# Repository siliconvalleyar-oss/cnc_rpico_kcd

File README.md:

# CNC RPico

Controlador CNC basado en Raspberry Pi Pico, diseñado en KiCad.

## Descripción

Proyecto de hardware para control de máquinas CNC utilizando la Raspberry Pi Pico como microcontrolador principal.

## Herramientas

- KiCad 10.0.4
- FreeRouting (autoroute)

## Licencia

GPL v2+

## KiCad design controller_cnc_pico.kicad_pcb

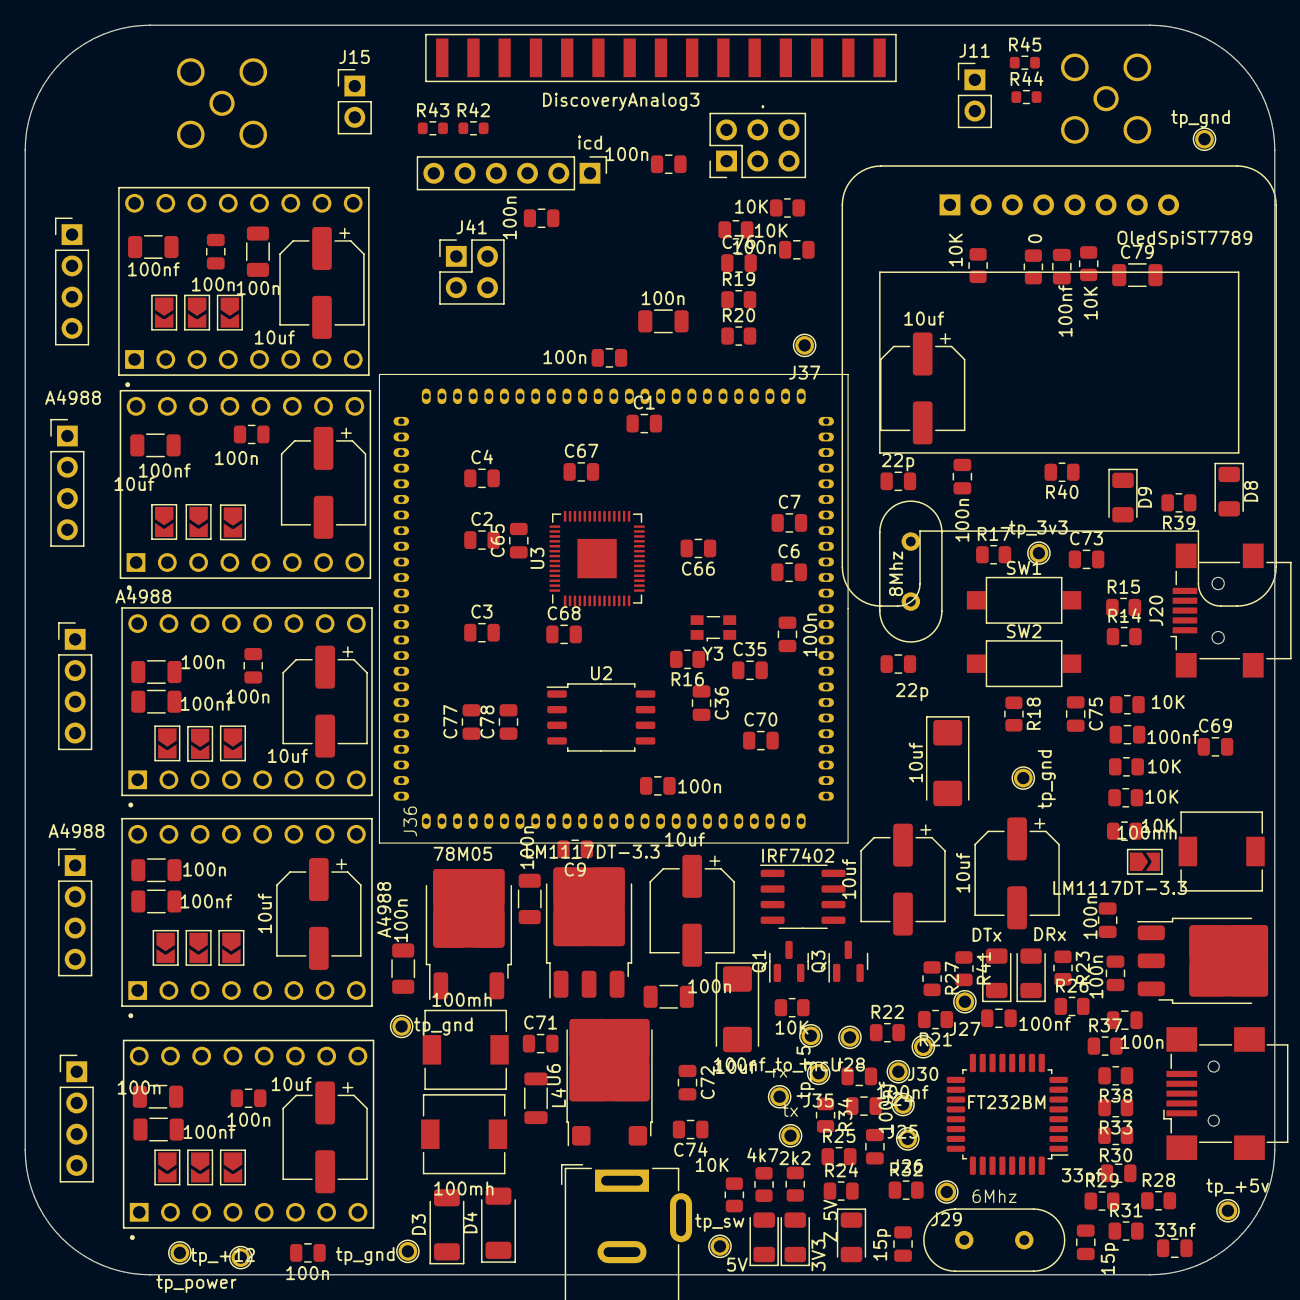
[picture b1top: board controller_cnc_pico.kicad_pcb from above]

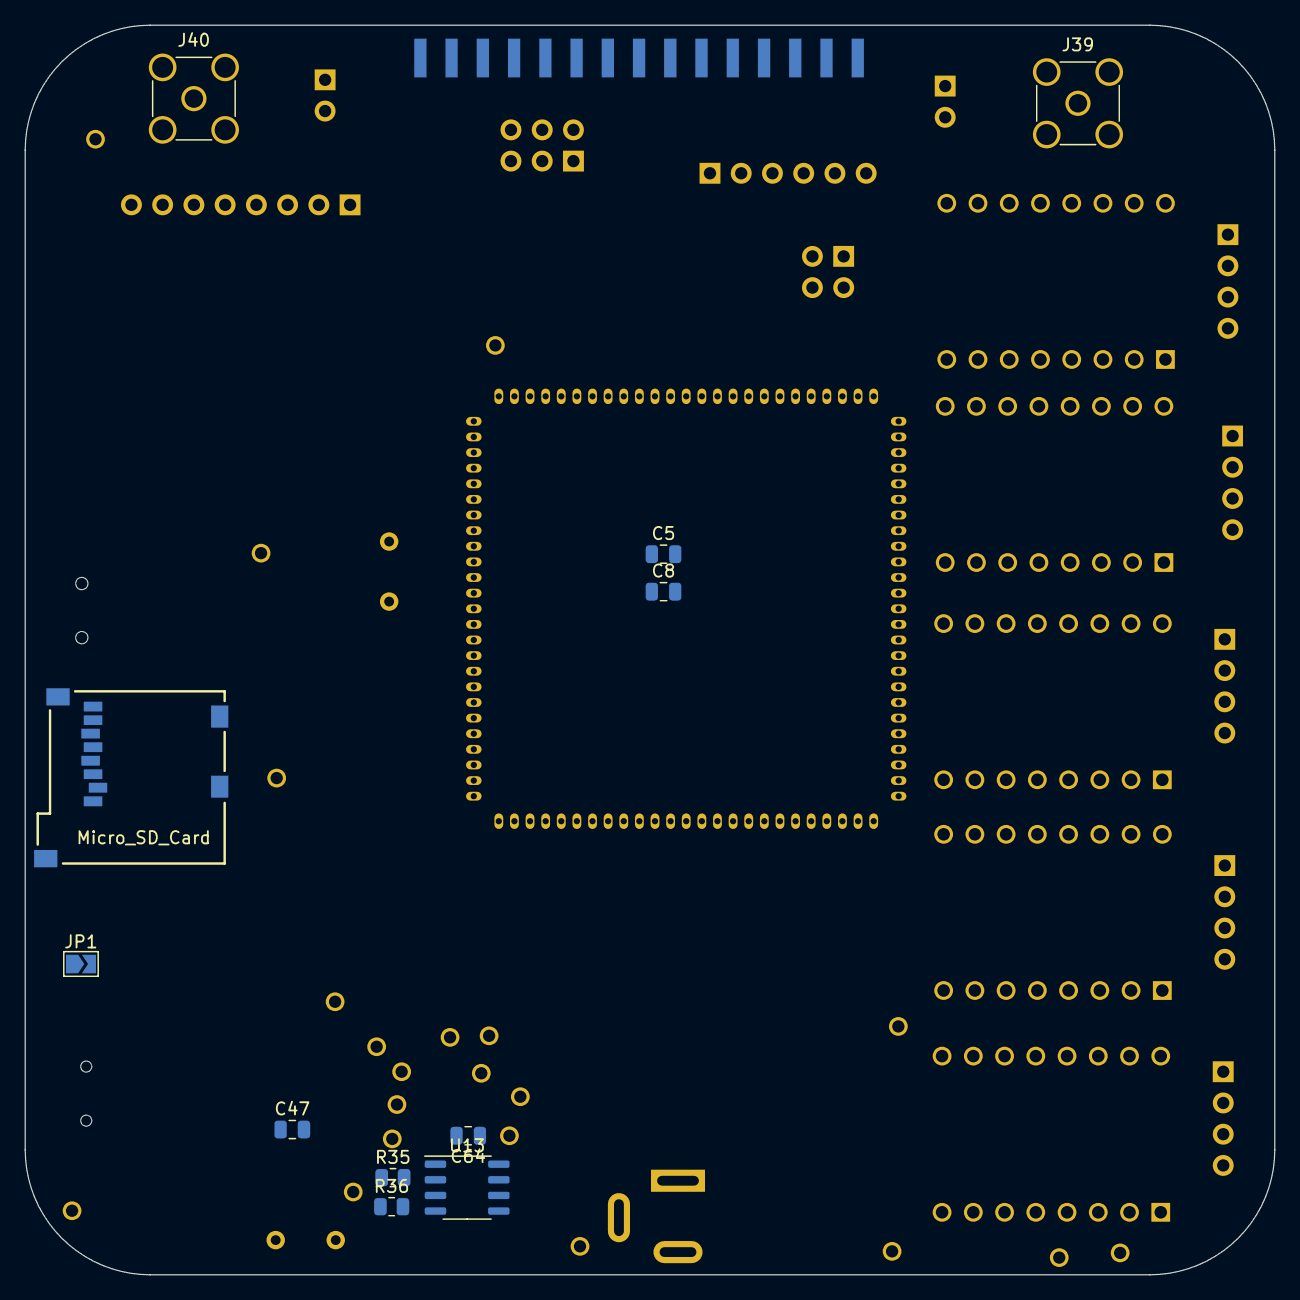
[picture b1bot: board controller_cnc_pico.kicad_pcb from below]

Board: 2 copper layers, 101.6 x 101.6 mm, 215 parts (11 on the bottom side), 161 nets, no tracks yet.

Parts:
C1, C2, C3, C4, C5, C6, C7, C8, C9, C10, C23, C24, C25, C26, C27, C28, C29, C32, C33, C46, C47, C59, C60, C62, C63, C77: 100n; C_0805_2012Metric
C11, C14, C15, C30, C49, C51, C53, C55, C57: 10uf; CP_Elec_6.3x5.4
C12, C31: 10uf; CP_EIA-6032-20_AVX-F
C13, C16, C17, C18, C19, C20, C21, C22: 100n; C_1206_3216Metric
C34, C39, C40, C41, C61, C64, C72, C74: 100nf; C_0805_2012Metric
C35, C36, C65, C66, C67, C68, C69, C70, C71, C73, C75, C76: 10n; C_0805_2012Metric
C37, C38: 22p; C_0805_2012Metric
C42, C43: 33nf; C_0805_2012Metric
C44, C45: 15p; C_0805_2012Metric
C48, C50, C52, C54, C56, C79: 100nf; C_1206_3216Metric
C58: 100nf_to_mclr; C_0805_2012Metric
C78: 1u; C_0805_2012Metric
D1: 5V; D_1206_3216Metric
D2: 3V3; D_1206_3216Metric
D3, D4: 1N4007; D_SOD-128
D5: Z 5V; D_1206_3216Metric
D6: DTx; D_1206_3216Metric
D7: DRx; D_1206_3216Metric
D8, D9: 1N4148; D_1206_3216Metric
DiscoveryAnalog3: DiscoveryAnalog3; PinHeader_2x15_P2.54mm_Vertical_edge_mount_smd
J1, J31, J32, J33, J34: PinHeader_1x04_P2.54mm_Vertical
J2: BarrelJack_Wuerth_6941xx301002
J3: tp_sw; Pin_D1.5mmx1mm
J4: tp_power; Pin_D1.5mmx1mm
J5: icd; PinHeader_1x06_P2.54mm_Vertical
J6: rx; Pin_D1.5mmx1mm
J7, J8, J9, J10: tp_gnd; Pin_D1.5mmx1mm
J11: jumper_gnd_ch1; PinHeader_1x02_P2.54mm_Vertical
J12: tp_+12; Pin_D1.5mmx1mm
J13: tp_+5; Pin_D1.5mmx1mm
J14: tp_3v3; Pin_D1.5mmx1mm
J15: jumper_gnd_ch2; PinHeader_1x02_P2.54mm_Vertical
J16: .; PinHeader_2x03_P2.54mm_Vertical
J17: OledSpiST7789; Adafruit_SSD1306_No_Mounting_Holes_pads
J18: Micro_SD_Card; 3M_2908-05WB-MG
J20: USB_B_Mini; USB_Mini-B_Lumberg_2486_01_Horizontal
J21: tx; Pin_D1.5mmx1mm
J22: tp_+5v; Pin_D1.5mmx1mm
J23: .; USB_Mini-B_Wuerth_65100516121_Horizontal
J24: ri; Pin_D1.5mmx1mm
J25: dcd; Pin_D1.5mmx1mm
J26: drs; Pin_D1.5mmx1mm
J27: txd; Pin_D1.5mmx1mm
J28: pwr_en; Pin_D1.5mmx1mm
J29: rst; Pin_D1.5mmx1mm
J30: dtr; Pin_D1.5mmx1mm
J35: cts; Pin_D1.5mmx1mm
J36: PIM_Socket; PIM100
J37: swd; Pin_D1.5mmx1mm
J39: osciloscope_ch2; SMA_Amphenol_901-144_Vertical
J40: osciloscope_ch1; SMA_Amphenol_901-144_Vertical
J41: Oscilllscope; PinHeader_2x02_P2.54mm_Vertical
JP1, JP2, JP3, JP4, JP5, JP6, JP7, JP8, JP9, JP10, JP11, JP12, JP13, JP14, JP15, JP16, JP17: SolderJumper-2_P1.3mm_Open_TrianglePad1.0x1.5mm
L1, L2, L3: 100mh; L_6.3x6.3_H3
L4: 100mh; L_1206_3216Metric
Q1, Q3: 2N7002; SOT-23
Q2: IRF7402; SOIC-8_3.9x4.9mm_P1.27mm
R1, R31: 4k7; R_0805_2012Metric
R2, R4, R5, R6, R8, R9, R10, R11, R12, R13: 10K; R_0805_2012Metric
R3, R23, R35, R41: 2k2; R_0805_2012Metric
R7, R21, R22, R26, R27, R37: 0; R_0805_2012Metric
R14, R15, R16, R17, R18, R19, R20, R29, R32, R36: 10k; R_0805_2012Metric
R24, R25, R34: 100; R_0805_2012Metric
R28: 470r; R_0805_2012Metric
R30: 1k5; R_0805_2012Metric
R33, R38: 27; R_0805_2012Metric
R39, R40: 50; R_0805_2012Metric
R42, R44: 10k; R_0603_1608Metric
R43, R45: 1k; R_0603_1608Metric
SW1, SW2: run; SW_SPST_CK_RS282G05A3
U1, U9, U10, U11, U12: A4988; MODULE_A4988_STEPPER_MOTOR_DRIVER_CARRIER
U2: W25Q32JVSS; SOIC-8_5.23x5.23mm_P1.27mm
U3: RP2040; QFN-56-1EP_7x7mm_P0.4mm_EP3.2x3.2mm
U4: 78M05; TO-252-2
U5, U8: LM1117DT-3.3; TO-252-3_TabPin2
U6: R-78E3.3-0.5; ATPAK-2
U7: FT232BM; LQFP-32_7x7mm_P0.8mm
U13: 93CxxA; SO-8_3.9x4.9mm_P1.27mm
Y1: 8Mhz; Crystal_HC49-4H_Vertical
Y2: 6Mhz; Crystal_HC49-4H_Vertical
Y3: 12MHz; Oscillator_SMD_SeikoEpson_SG3030CM

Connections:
3v3_out: C43.1, U7.6 (3V3OUT)
+1V0: C65.2, C66.2, U3.23 (DVDD), U3.45 (VREG_VOUT), U3.50 (DVDD)
+3.3V: C1.1, C2.1, C3.1, C4.1, C5.1, C6.1, C7.1, C8.1, C9.1, C22.1, C24.1, C25.1, C27.1, C29.1, C31.1, C32.1, C34.1, C61.1, C62.1, C79.1, D8.1 (K), J5.2, J14.1, J16.1, J18.4 (VDD), J36.2 (VDD), J36.16 (VDD), J36.37 (VDD), J36.62 (VDD), J36.86 (VDD), R3.2, R5.2, R6.2, R8.1, R9.2, R10.2, R11.2, R12.2, R13.1, U2.8 (VCC), U5.2 (VO)
+3.3VA: C67.2, C68.2, C69.2, C70.2, C74.2, C77.2, C78.2, R17.2, R18.2, U3.1 (IOVDD), U3.10 (IOVDD), U3.22 (IOVDD), U3.33 (IOVDD), U3.42 (IOVDD), U3.44 (VREG_IN), U3.48 (USB_VDD), U3.49 (IOVDD), U6.3 (OUT)
+3V3: C40.2, C41.2, C47.2, C59.2, C64.1, JP1.2 (B), R23.2, R26.2, R27.1, R32.1, R36.1, R37.1, R41.2, U7.13 (VCCIO), U8.2 (VO), U13.8 (VCC)
+5V: C12.1, C13.1, C19.1, C23.1, C26.1, C28.1, C30.1, C33.1, C63.1, D5.1 (K), J13.1, J16.2, J16.4, J17.2, JP2.1 (A), JP3.1 (A), JP4.1 (A), JP5.1 (A), JP6.1 (A), JP7.1 (A), JP8.1 (A), JP9.1 (A), JP10.1 (A), JP11.1 (A), JP12.1 (A), JP13.1 (A), JP14.1 (A), JP15.1 (A), JP16.1 (A), JP17.1 (A), L2.2, R1.2, U1.5 (~RESET), U1.6 (~SLEEP), U1.10 (VDD), U5.3 (VI), U9.5 (~RESET), U9.6 (~SLEEP), U9.10 (VDD), U10.5 (~RESET), U10.6 (~SLEEP), U10.10 (VDD), U11.5 (~RESET), U11.6 (~SLEEP), U11.10 (VDD), U12.5 (~RESET), U12.6 (~SLEEP), U12.10 (VDD)
+12V: C14.1, C15.1, C16.1, C17.1, C18.1, C20.1, J12.1, Q2.5 (D), Q2.6 (D), Q2.7 (D), Q2.8 (D), U1.16 (VMOT), U4.1 (VI), U9.16 (VMOT), U10.16 (VMOT), U11.16 (VMOT), U12.16 (VMOT)
+15V: D3.2 (A), D4.2 (A), J2.1 (In)
/ft232/FT_CTS: C39.2, U7.22 (D3/~CTS)
/ft232/FT_PWR_EN: R22.2, U7.15 (~PWREN)
/ft232/FT_RST_OUT: R30.2, U7.5 (~RSTOUT)
/ft232/V+_USB: R28.1, R31.2, U7.3 (VCC), U7.26 (VCC)
/ft232/dtr_to_mclr: C58.2, U7.21 (D4/~DTR)
/ft232/ft_pwr_ctrl: R21.1, R27.2, U7.14 (PWRCTL)
/i2c/display/_SCL_OLED: J16.5, R5.1
/i2c/display/_SDA_OLED: J16.3, R6.1
/main/RPI_pico_w/piso_ws__reg_osc/run: C73.1, R17.1, SW1.2
/main/RPI_pico_w/piso_ws__reg_osc/usb_boot: C75.1, R18.1, SW2.2
/main/RPI_pico_w/run: J37.1, U3.26 (RUN)
/power/power_on_off: Q1.3 (D), Q2.4 (G), Q3.3 (D)
/power/signal rpi: J3.1, R4.2
/power/sw_power: C10.1, C11.1, J4.1, L1.2, Q2.1 (S), Q2.2 (S), Q2.3 (S)
AI1+/OSC1: J40.1, R44.2
AI1+/OSC2: J39.1, J41.2, R42.2
DAT1: J18.8 (DAT1), R10.1
DAT2: J18.1 (DAT2), R9.1
FT_EECS: U7.32 (EECS), U13.1 (CS)
FT_EEDATA: R35.2, U7.2 (EEDATA), U13.3 (DI)
FT_EESK: U7.1 (EESK), U13.2 (SCLK)
FT_XTIN: C45.1, U7.27 (XTIN), Y2.2
FT_XTOUT: C44.1, U7.28 (XTOUT), Y2.1
GND: C10.2, C11.2, C12.2, C13.2, C14.2, C15.2, C16.2, C17.2, C18.2, C19.2, C20.2, C21.2, C22.2, C23.2, C24.2, C25.2, C26.2, C27.2, C28.2, C29.2, C30.2, C31.2, C32.2, C33.2, C34.2, C35.2, C36.2, C37.2, C38.2, C40.1, C41.1, C42.2, C43.2, C44.2, C45.2, C46.1, C47.1, C48.2, C49.2, C50.2, C51.2, C52.2, C53.2, C54.2, C55.2, C56.2, C57.2, C59.1, C60.1, C61.2, C62.2, C63.2, C64.2, C65.1, C66.1, C67.1, C68.1, C69.1, C70.1, C71.2, C72.1, C73.2, C74.1, C75.2, C76.2, C77.1, C78.1, C79.2, D1.1 (K), D2.1 (K), D5.2 (A), D9.2 (A), DiscoveryAnalog3.5 (GND), DiscoveryAnalog3.6 (GND), DiscoveryAnalog3.11 (GND), DiscoveryAnalog3.12 (GND), J2.2 (Ext), J5.3, J7.1, J8.1, J9.1, J10.1, J11.2, J15.2, J16.6, J17.1, J18.6 (VSS), J20.5 (GND), J20.6 (Shield), J23.5 (GND), J23.6 (Shield), J36.15 (VSS), J36.36 (VSS), J36.45 (VSS), J36.46 (VSS), J36.65 (VSS), J36.75 (VSS), J41.3, J41.4, Q1.2 (S), Q3.2 (S), R21.2, R29.2, R43.1, R45.1, SW1.1, SW2.1, U1.9 (GND), U1.15 (GND), U2.4 (GND), U3.19 (TESTEN), U3.57 (GND), U4.2 (GND), U5.1 (GND), U6.2 (GND), U7.9 (GND), U7.17 (GND), U7.29 (AGND), U7.31 (TEST), U8.1 (GND), U9.9 (GND), U9.15 (GND), U10.9 (GND), U10.15 (GND), U11.9 (GND), U11.15 (GND), U12.9 (GND), U12.15 (GND), U13.5 (GND), Y3.2, Y3.4
M_RX: J6.1, R24.1
M_TX: J21.1, R25.1
unnamed: C1.2, C4.2, C7.2
unnamed: C2.2, C5.2, C8.2
unnamed: C3.2, C6.2, C9.2
unnamed: C36.1, R16.1, Y3.1
unnamed: D1.2 (A), R1.1
unnamed: D2.2 (A), R3.1
unnamed: D3.1 (K), D4.1 (K), L1.1
unnamed: D6.2 (A), R41.1
unnamed: D6.1 (K), U7.12 (~TXLED)
unnamed: D7.2 (A), R23.1
unnamed: D7.1 (K), U7.11 (~RXLED)
unnamed: D8.2 (A), D9.1 (K), R39.2, R40.1
unnamed: DiscoveryAnalog3.2 (AI1+/OSC1), R44.1, R45.2
unnamed: DiscoveryAnalog3.4 (AI2+/OSC2), R42.1, R43.2
unnamed: DiscoveryAnalog3.1 (GND/AI1-), J11.1, J40.2
unnamed: DiscoveryAnalog3.3 (GND/AI2-), J15.1, J39.2
unnamed: J1.1, U1.14 (2B)
unnamed: J1.2, U1.13 (2A)
unnamed: J1.3, U1.11 (1B)
unnamed: J1.4, U1.12 (1A)
unnamed: J18.3 (CMD), R7.1, R8.2
unnamed: J20.3 (D+), R15.1
unnamed: J20.2 (D-), R14.1
unnamed: J23.3 (D+), R38.1
unnamed: J23.2 (D-), R33.1
unnamed: J23.1 (VBUS), L3.1
unnamed: J31.1, U9.14 (2B)
unnamed: J31.2, U9.13 (2A)
unnamed: J31.3, U9.11 (1B)
unnamed: J31.4, U9.12 (1A)
unnamed: J32.1, U10.14 (2B)
unnamed: J32.2, U10.13 (2A)
unnamed: J32.3, U10.11 (1B)
unnamed: J32.4, U10.12 (1A)
unnamed: J33.1, U11.14 (2B)
unnamed: J33.2, U11.13 (2A)
unnamed: J33.3, U11.11 (1B)
unnamed: J33.4, U11.12 (1A)
unnamed: J34.1, U12.14 (2B)
unnamed: J34.2, U12.13 (2A)
unnamed: J34.3, U12.11 (1B)
unnamed: J34.4, U12.12 (1A)
unnamed: JP2.2 (B), U1.2 (MS1)
unnamed: JP3.2 (B), U1.3 (MS2)
unnamed: JP4.2 (B), U1.4 (MS3)
unnamed: JP5.2 (B), U12.2 (MS1)
unnamed: JP6.2 (B), U12.3 (MS2)
unnamed: JP7.2 (B), U12.4 (MS3)
unnamed: JP8.2 (B), U10.2 (MS1)
unnamed: JP9.2 (B), U10.3 (MS2)
unnamed: JP10.2 (B), U10.4 (MS3)
unnamed: JP11.2 (B), U11.2 (MS1)
unnamed: JP12.2 (B), U11.3 (MS2)
unnamed: JP13.2 (B), U11.4 (MS3)
unnamed: JP14.2 (B), U9.2 (MS1)
unnamed: JP15.2 (B), U9.3 (MS2)
unnamed: JP16.2 (B), U9.4 (MS3)
unnamed: Q1.1 (G), R2.1
unnamed: Q3.1 (G), R4.1
unnamed: R19.2, R20.1
unnamed: C48.1, C49.1, U1.1 (~ENABLE)
unnamed: C76.1, R19.1, U3.43 (ADC_AVDD)
unnamed: R14.2, U3.46 (USB_DM)
unnamed: R15.2, U3.47 (USB_DP)
unnamed: C21.1, L2.1, U4.3 (VO)
unnamed: C72.2, L4.2, U6.1 (IN)
unnamed: C42.1, R28.2, U7.30 (AVCC)
unnamed: R24.2, U7.25 (D0/TXD)
unnamed: R25.2, U7.24 (D1/RXD)
unnamed: R26.1, U7.10 (~SLEEP)
unnamed: C50.1, C51.1, U9.1 (~ENABLE)
unnamed: C54.1, C55.1, U10.1 (~ENABLE)
unnamed: C52.1, C53.1, U11.1 (~ENABLE)
unnamed: C56.1, C57.1, U12.1 (~ENABLE)
unnamed: R35.1, R36.2, U13.4 (DO)
RB0: J18.7 (DAT0), R11.1
RB1: J18.5 (CLK), R12.1
USB_D+: R33.2, U7.8 (USBDM)
USB_D-: R30.1, R38.2, U7.7 (USBDP)
V+_USB: C46.2, C60.2, J22.1, JP1.1 (A), JP17.2 (B), L3.2, U8.3 (VI)
ft_cts: C39.1, J35.1, R34.1
ft_dcd: J25.1, U7.19 (D6/~DCD)
ft_drs: J26.1, U7.20 (D5/~DSR)
ft_pwr_en: J28.1, R22.1
ft_reset: R29.1, R31.1, R32.2, U7.4 (~RESET)
ft_ri: J24.1, U7.18 (D7/~RI)
ft_rst: J29.1, R34.2, R37.2, U7.23 (D2/~RST)
ft_txd_en: J27.1, U7.16 (TXDEN)
mclr: C58.1, J5.1, J36.13 (MCLR), R40.2
osc1: C35.1, C38.1, J36.63 (OSC1/CLKI/RC12), U3.20 (XIN), Y1.2, Y3.3
osc2: C37.1, J36.64 (OSC2/CLKO/RC15), R16.2, U3.21 (XOUT), Y1.1
pgc: J5.5, J36.24 (PGEC1/AN1/CN3/RB1)
pgd: J5.4, J36.25 (PGED1/AN0/CN2/RB0)
qspi_sclk: U2.6 (CLK), U3.52 (QSPI_SCLK)
qspi_sd0: U2.5 (DI(IO0)), U3.53 (QSPI_SD0)
qspi_sd1: U2.2 (DO(IO1)), U3.55 (QSPI_SD1)
qspi_sd2: U2.3 (IO2), U3.54 (QSPI_SD2)
qspi_sd3: U2.7 (IO3), U3.51 (QSPI_SD3)
qspi_ss: U2.1 (~CS), U3.56 (QSPI_SS)
ra0: J36.69 (AERXERR/RG15), U3.14 (GPIO11)
ra2: J36.4 (PMD6/RE6), U3.16 (GPIO13)
ra3: J36.5 (PMD7/RE7), U3.17 (GPIO14)
ra4: J36.6 (T2CK/RC1), U3.18 (GPIO15)
ra5: J36.7 (T3CK/AC2TX/RC2), U3.27 (GPIO16)
ra6: J36.8 (T4CK/AC2RX/RC3), U3.28 (GPIO17)
ra7: J36.9 (T5CK/SDI1/RC4), J36.54 (T5CK/SDI1/RC4), U3.29 (GPIO18)
ra9: J36.10 (ECOL/SCK2/U6TX/U3RTS/PMA5/CN8/RG6), U3.30 (GPIO19)
ra10: J36.11 (ECRS/SDA4/SDI2/U3RX/PMA4/CN9/RG7), U3.31 (GPIO20)
ra14: J36.12 (ERXDV/AERXDV/ECRSDV/AECRSDV/SCL4/SDO2/U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), U3.32 (GPIO21)
ra15: J36.14 (ERXCLK/AERXCLK/EREFCLK/AEREFCLK/SS2/U6R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), U3.34 (GPIO22)
rb10: J36.56 (AETXEN/SDA1/INT4/RA15), J36.67 (AETXEN/SDA1/INT4/RA15)
rc2: J36.20 (AN2/C2IN-/CN4/RB2), U3.3 (GPIO1)
rc3: J36.23 (SS1/IC2/RD9), U3.4 (GPIO2)
rc4: J36.19 (AERXD1/INT2/RE9), U3.5 (GPIO3)
rc13: J36.96 (AN5/C1IN+/VBUSON/CN7/RB5), U3.7 (GPIO5)
rc14: J36.21 (AN4/C1IN-/CN6/RB4), U3.8 (GPIO6)
rd1: J36.72 (SDO1/OC1/INT0/RD0), J36.73 (SOSCI/CN1/RC13), J36.74 (SOSCO/T1CK/CN0/RC14)
re0: J36.28 (VREF-/CVREF-/AERXD2/PMA7/RA9), U3.9 (GPIO7)
re1: J36.29 (VREF+/CVREF+/AERXD3/PMA6/RA10), U3.11 (GPIO8)
re7: J36.39 (AC1TX/SCK4/U5TX/U2RTS/RF13), U3.35 (GPIO23)
re8: J36.40 (AC1RX/SS4/U5RX/U2CTS/RF12), U3.36 (GPIO24)
re9: J36.41 (AN12/ERXD0/AECRS/PMA11/RB12), U3.37 (GPIO25)
rf1: J36.88 (C1TX/ETXD0/PMD10/RF1), J36.94 (PMD1/RE1)
rf8: J36.99 (PMD3/RE3), J36.100 (PMD4/RE4)
rg14: J36.17 (TMS/RA0), J36.18 (AERXD0/INT1/RE8), J36.66 (AERXD0/INT1/RE8)
trigger_out: DiscoveryAnalog3.9 (INT/CLK1), DiscoveryAnalog3.13 (Trigger_Out)
vcc: C71.1, L4.1
